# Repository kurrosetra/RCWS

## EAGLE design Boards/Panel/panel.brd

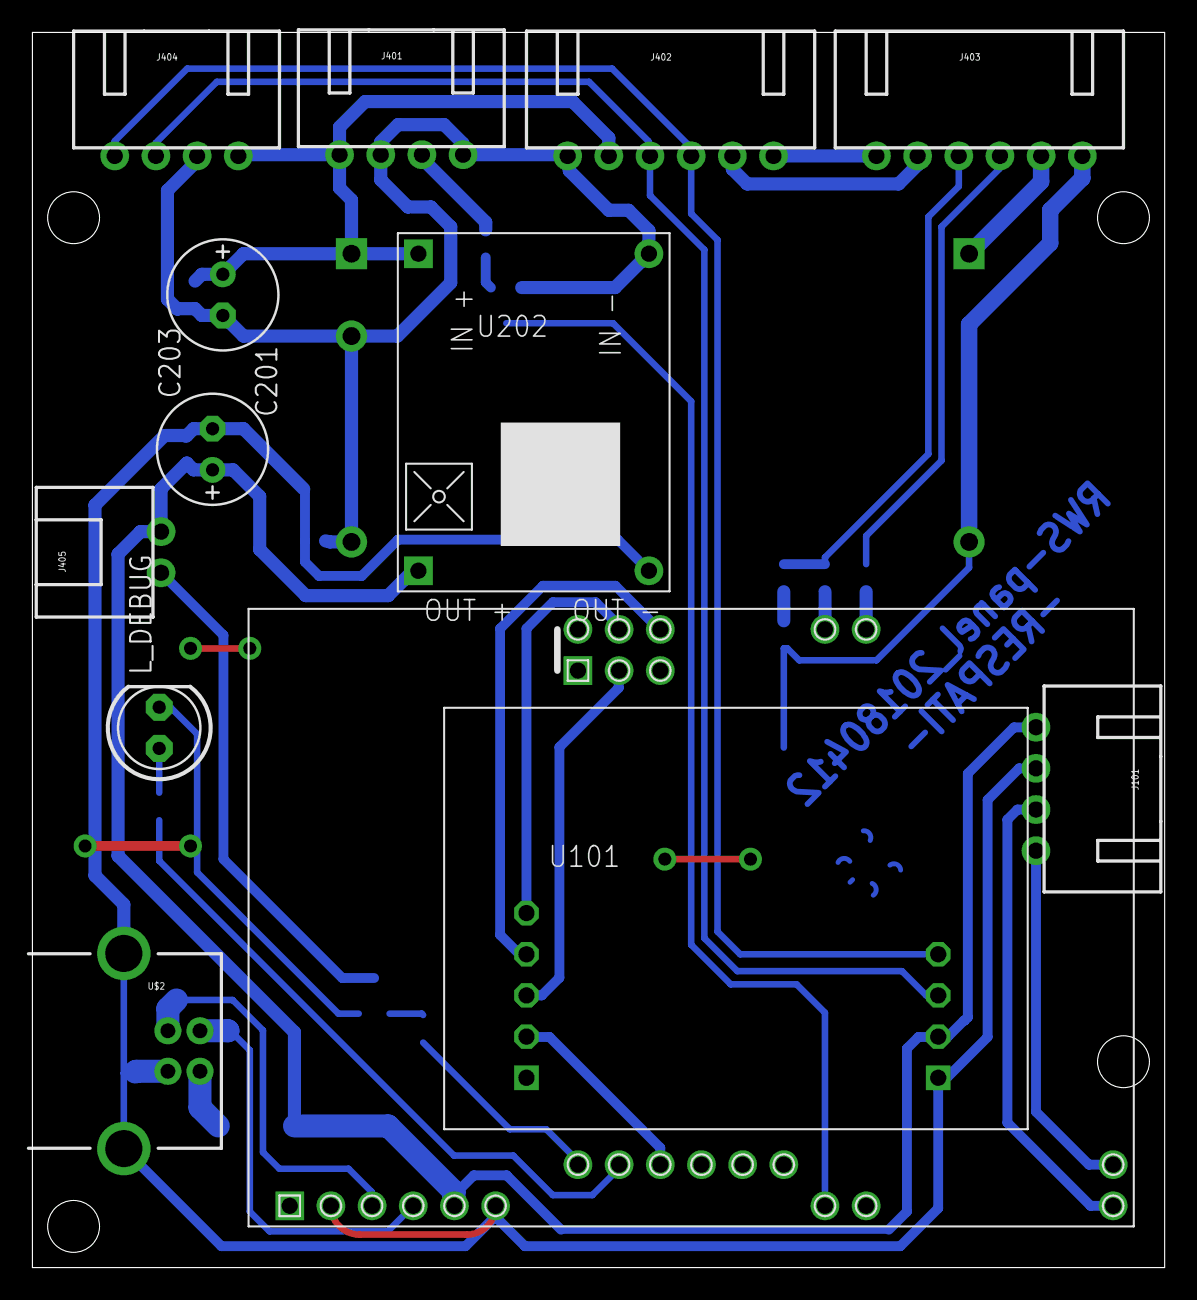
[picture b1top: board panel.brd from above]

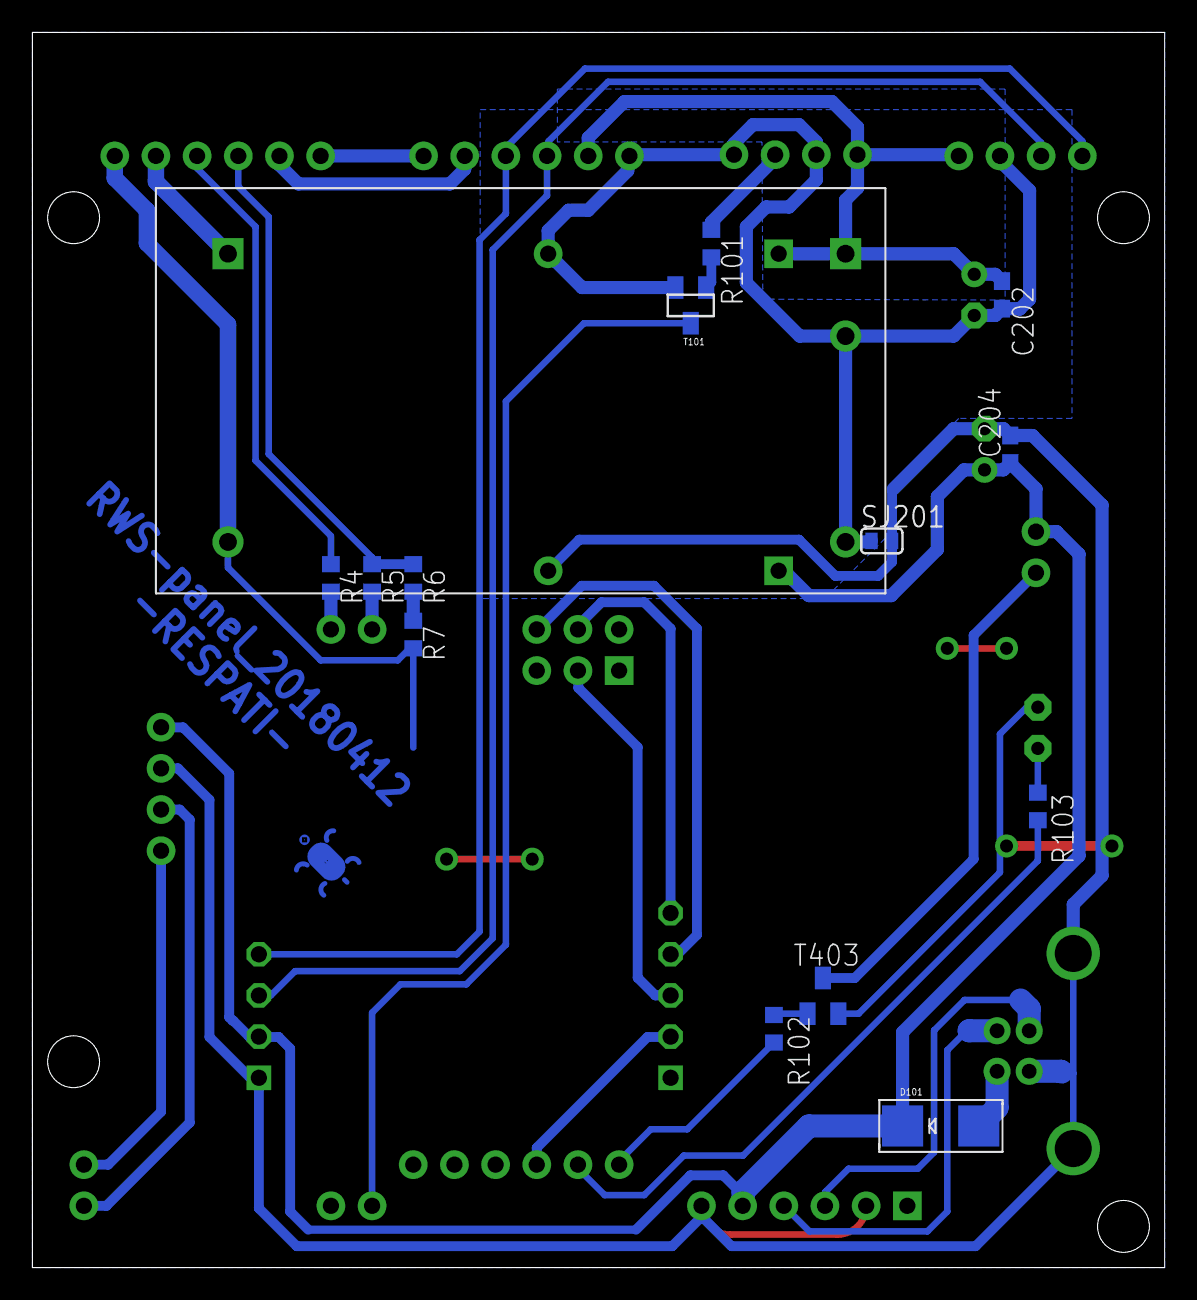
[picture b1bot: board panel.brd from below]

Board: 2 copper layers, 69.8 x 76.2 mm, 33 parts (13 on the bottom side), 31 nets.

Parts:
C201: 47uF/50V; E2,5-7
C202, C204: 100n; C0603
C203: 100uF/25V; E2,5-7
D101: 1N5822; SMADIODE
J101: RESV; XH-4-RA
J401: POWER_IN; XH-4-RA
J402: OPTRONIK; XH-6-RA
J403: JETSON; XH-6-RA
J404: JOYSTICK+MONITOR; XH-4-RA
J405: INDICATOR; XH-2-RA
L_DEBUG: LED5MM
R4, R101: 100; R0603
R5, R6, R7, R102, R103: 1k; R0603
SJ201: SJS
T101: MMBT2222A; SOT23
T403: SOT23-BEC
U1: MCP2515_CAN2
U101: MODULE_MEGA2560; MOD_MEGA_LAYOUT
U201: PSU_5V; MP1584_MIN
U202: PSU_12V; MOD_LM2596
U$1: KURRO_FOOTPRINT; KURRO-LOGO
U$2: USB+SHIELD; USB-B-PTH
U$3: MOD_MEGA_LAYOUT_SERIAL1
U$4: MOD_MEGA_LAYOUT_SERIAL2
U$5: MOD_MEGA_LAYOUT_SERIAL3
U$6: MOD_MEGA_LAYOUT_ICSP
U$7: MOD_MEGA_LAYOUT_Y_EVEN

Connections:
+15V: J403.5, U202.2
+24V: C201.+, C202.1, J401.1, J402.2, J404.4, U201.1, U202.1
BUS_CANH: J402.3, J404.2, U1.3
BUS_CANL: J402.4, J404.1, U1.4
BUS_CS: U1.6, U$7.Y6
BUTTON_TX: J401.3, R101.1
BUTTON_TXD: T101.3, U$3.Y16
GND: C203.-, C204.2, J101.2, J403.6, L_DEBUG.K, R7.2, SJ201.2, T403.E, U1.1, U101.P2, U101.P6, U201.4, U202.4, U$2.GND, U$2.S1, U$2.S2
INDICATOR_RTN: J405.1, T403.C
JETSON_RX: J403.3, R5.1, R6.1
JETSON_RXD: R5.2, U$4.X5
JETSON_TX: J403.4, R4.1
JETSON_TXD: R4.2, U$4.X8
MISO: U1.8, U$6.S6
MOSI: U1.7, U$6.S3
unnamed: R102.1, T403.B
unnamed: U101.P3, U$2.D+
unnamed: U101.P4, U$2.D-
unnamed: D101.A, U$2.VBUS
unnamed: R102.2, U$7.Y2
unnamed: R101.2, T101.1
unnamed: L_DEBUG.A, R103.1
unnamed: R103.2, U$7.Y4
unnamed: R6.2, R7.1
RESV_RXD: J101.4, U$5.Z10
RESV_TXD: J101.3, U$5.Z9
SCK: U1.9, U$6.S4
V-: C201.-, C202.2, J401.2, J401.4, J402.1, J404.3, SJ201.1, T101.2, U201.2, U202.3, U202.5
VCC: C203.+, C204.1, D101.C, J101.1, J405.2, U1.2, U101.P5, U201.3
VIDEO+: J402.5, J403.2
VIDEO-: J402.6, J403.1

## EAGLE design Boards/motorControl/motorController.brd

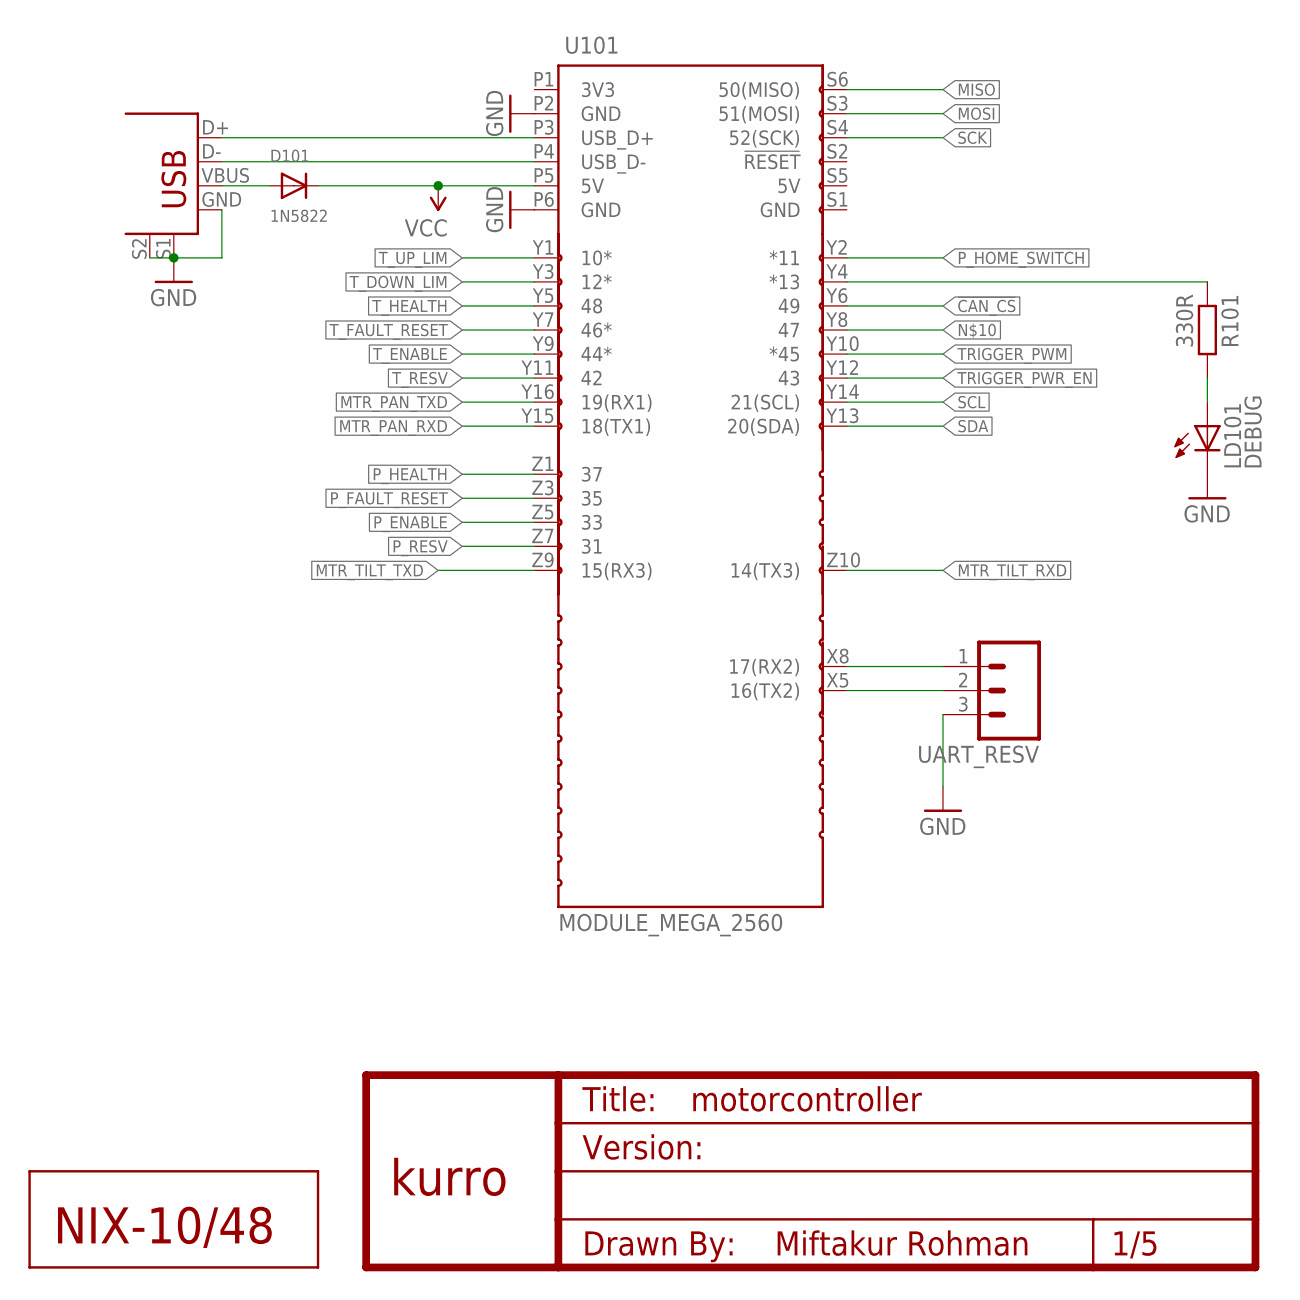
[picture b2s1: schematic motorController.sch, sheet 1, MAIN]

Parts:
D101: 1N5822; SMADIODE
J101: USB+SHIELD; USB-B-PTH
LD101: DEBUG; LED5MM
R101: 330R; R0603
U101: MODULE_MEGA_2560; MOD_MEGA_LAYOUT
U$1: KURRO_FOOTPRINT; KURRO-LOGO
U$2: NIX; NIX-XX/XXX
U$3: MOD_MEGA_LAYOUT_ICSP
U$4: MOD_MEGA_LAYOUT_SERIAL1
U$5: MOD_MEGA_LAYOUT_SERIAL2
U$6: MOD_MEGA_LAYOUT_SERIAL3
U$7: MOD_MEGA_LAYOUT_Y_EVEN
U$8: MOD_MEGA_LAYOUT_Y_ODD
U$9: MOD_MEGA_LAYOUT_Z_ODD
U$10: MOD_MEGA_LAYOUT_I2C
UART_RESV: M03LOCK; 1X03_LOCK

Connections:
!CAN_CS: U$7.Y6 (49); also elsewhere on the board
GND: J101.GND, J101.S1, J101.S2, LD101.K (C), U101.P2 (GND), U101.P6 (GND), UART_RESV.3; also elsewhere on the board
MISO: U$3.S6 (50(MISO)); also elsewhere on the board
MOSI: U$3.S3 (51(MOSI)); also elsewhere on the board
MTR_PAN_RXD: U$4.Y15 (18(TX1)); also elsewhere on the board
MTR_PAN_TXD: U$4.Y16 (19(RX1)); also elsewhere on the board
MTR_TILT_RXD: U$6.Z10 (14(TX3)); also elsewhere on the board
MTR_TILT_TXD: U$6.Z9 (15(RX3)); also elsewhere on the board
unnamed: LD101.A, R101.2
unnamed: J101.D+, U101.P3 (USB_D+)
unnamed: R101.1, U$7.Y4 (*13)
unnamed: J101.D-, U101.P4 (USB_D-)
unnamed: D101.A, J101.VBUS
P_ENABLE: U$9.Z5 (33); also elsewhere on the board
P_FAULT_RESET: U$9.Z3 (35); also elsewhere on the board
P_HEALTH: U$9.Z1 (37); also elsewhere on the board
P_HOME_SWITCH: U$7.Y2 (*11); also elsewhere on the board
P_RESV: U$9.Z7 (31); also elsewhere on the board
RXD2: U$5.X8 (17(RX2)), UART_RESV.1
SCK: U$3.S4 (52(SCK)); also elsewhere on the board
SCL: U$10.Y14 (21(SCL))
SDA: U$10.Y13 (20(SDA))
TRIGGER_PWM: U$7.Y10 (*45); also elsewhere on the board
TRIGGER_PWR_EN: U$7.Y12 (43); also elsewhere on the board
TXD2: U$5.X5 (16(TX2)), UART_RESV.2
T_DOWN_LIM: U$8.Y3 (12*); also elsewhere on the board
T_ENABLE: U$8.Y9 (44*); also elsewhere on the board
T_FAULT_RESET: U$8.Y7 (46*); also elsewhere on the board
T_HEALTH: U$8.Y5 (48); also elsewhere on the board
T_RESV: U$8.Y11 (42); also elsewhere on the board
T_UP_LIM: U$8.Y1 (10*); also elsewhere on the board
VCC: D101.C, U101.P5 (5V); also elsewhere on the board

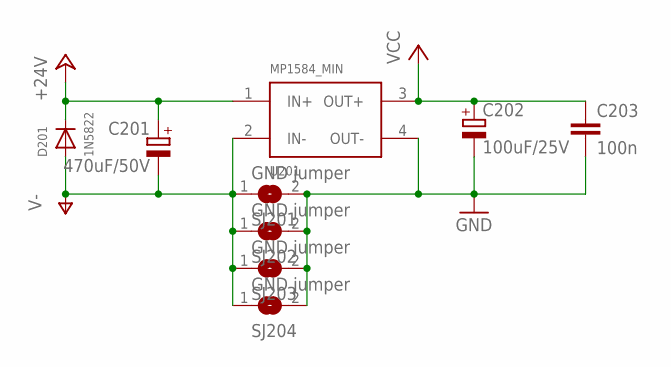
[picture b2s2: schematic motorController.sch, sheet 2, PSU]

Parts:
C201: 470uF/50V; E5-10,5
C202: 100uF/25V; E5-10,5
C203: 100n; C0603
D201: 1N5822; SMADIODE
SJ201, SJ202, SJ203, SJ204: GND jumper; SJS
U201: MP1584_MIN

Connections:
+24V: C201.+, D201.C, U201.1 (IN+); also elsewhere on the board
GND: C202.-, C203.2, SJ201.2, SJ202.2, SJ203.2, SJ204.2, U201.4 (OUT-); also elsewhere on the board
V-: C201.-, D201.A, SJ201.1, SJ202.1, SJ203.1, SJ204.1, U201.2 (IN-); also elsewhere on the board
VCC: C202.+, C203.1, U201.3 (OUT+); also elsewhere on the board

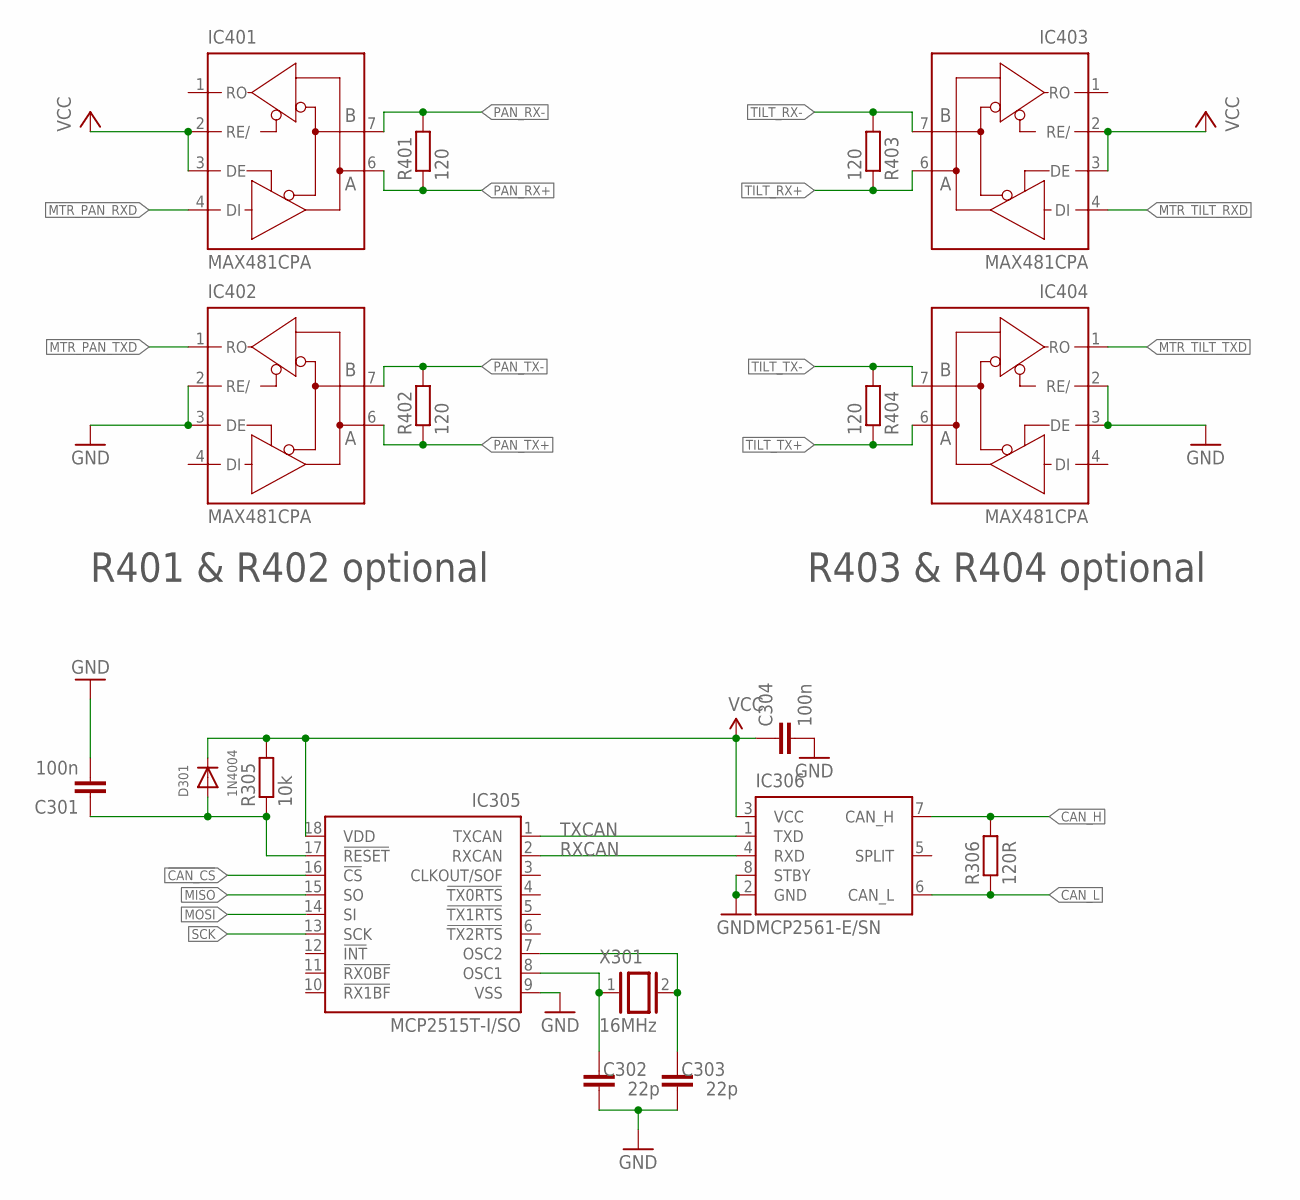
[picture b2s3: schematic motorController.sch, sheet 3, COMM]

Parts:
C301, C304: 100n; C0603
C302, C303: 22p; C0603
D301: 1N4004; SOD-323F
IC305: MCP2515T-I/SO; SO-18
IC306: MCP2561-E/SN; SOIC-8
IC401, IC402, IC403, IC404: MAX481CPA; DIL08
R305: 10k; R0603
R306: 120R; R0603
R401, R402, R403, R404: 120; R0603
X301: 16MHz; QS

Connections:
!CAN_CS: IC305.16 (!CS); also elsewhere on the board
CAN_H: IC306.7 (CAN_H), R306.2; also elsewhere on the board
CAN_L: IC306.6 (CAN_L), R306.1; also elsewhere on the board
GND: C301.2, C302.1, C303.1, C304.2, IC305.9 (VSS), IC306.2 (GND), IC306.8 (STBY), IC401.5 (GND), IC402.2 (RE/), IC402.3 (DE), IC402.5 (GND), IC403.5 (GND), IC404.2 (RE/), IC404.3 (DE), IC404.5 (GND); also elsewhere on the board
MISO: IC305.15 (SO); also elsewhere on the board
MOSI: IC305.14 (SI); also elsewhere on the board
MTR_PAN_RXD: IC401.4 (DI); also elsewhere on the board
MTR_PAN_TXD: IC402.1 (RO); also elsewhere on the board
MTR_TILT_RXD: IC403.4 (DI); also elsewhere on the board
MTR_TILT_TXD: IC404.1 (RO); also elsewhere on the board
unnamed: C301.1, D301.A, IC305.17 (!RESET), R305.1
unnamed: C302.2, IC305.8 (OSC1), X301.1
unnamed: C303.2, IC305.7 (OSC2), X301.2
PAN_RX+: IC401.6 (A), R401.1; also elsewhere on the board
PAN_RX-: IC401.7 (B), R401.2; also elsewhere on the board
PAN_TX+: IC402.6 (A), R402.1; also elsewhere on the board
PAN_TX-: IC402.7 (B), R402.2; also elsewhere on the board
RXCAN: IC305.2 (RXCAN), IC306.4 (RXD)
SCK: IC305.13 (SCK); also elsewhere on the board
TILT_RX+: IC403.6 (A), R403.1; also elsewhere on the board
TILT_RX-: IC403.7 (B), R403.2; also elsewhere on the board
TILT_TX+: IC404.6 (A), R404.1; also elsewhere on the board
TILT_TX-: IC404.7 (B), R404.2; also elsewhere on the board
TXCAN: IC305.1 (TXCAN), IC306.1 (TXD)
VCC: C304.1, D301.C, IC305.18 (VDD), IC306.3 (VCC), IC401.2 (RE/), IC401.3 (DE), IC401.8 (VCC), IC402.8 (VCC), IC403.2 (RE/), IC403.3 (DE), IC403.8 (VCC), IC404.8 (VCC), R305.2; also elsewhere on the board

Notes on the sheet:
R401 & R402 optional
R403 & R404 optional

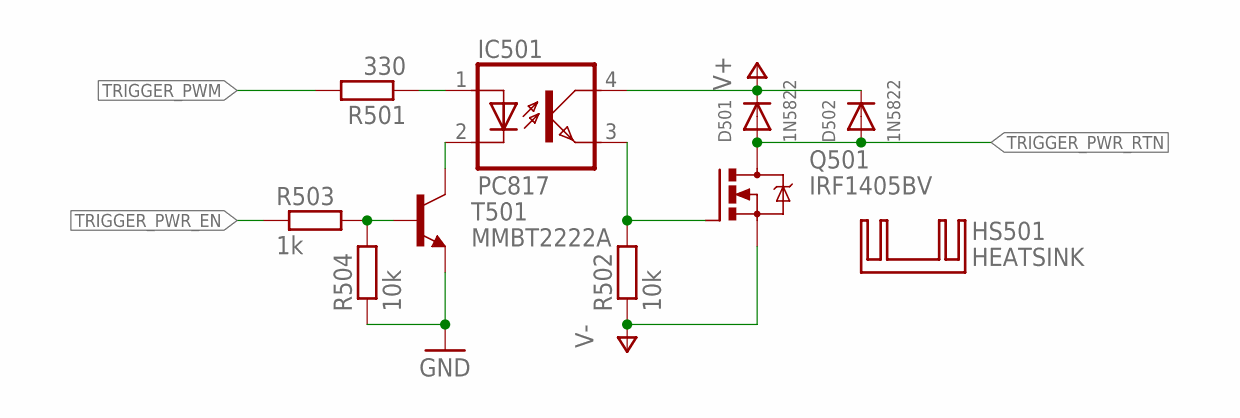
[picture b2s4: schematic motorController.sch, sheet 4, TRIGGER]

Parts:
D501, D502: 1N5822; SMADIODE
HS501: HEATSINK; BV_150X105
IC501: PC817; DIL04
Q501: IRF1405BV; TO220BV
R501: 330; R0603
R502, R504: 10k; R0603
R503: 1k; R0603
T501: MMBT2222A; SOT23

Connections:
GND: R504.1, T501.2 (E); also elsewhere on the board
unnamed: IC501.2 (C), T501.3 (C)
unnamed: R503.2, R504.2, T501.1 (B)
unnamed: IC501.1 (A), R501.1
unnamed: IC501.3 (EMIT), Q501.G, R502.2
TRIGGER_PWM: R501.2; also elsewhere on the board
TRIGGER_PWR_EN: R503.1; also elsewhere on the board
TRIGGER_PWR_RTN: D501.A, D502.A, Q501.D; also elsewhere on the board
V+: D501.C, D502.C, IC501.4 (COL); also elsewhere on the board
V-: Q501.S, R502.1; also elsewhere on the board

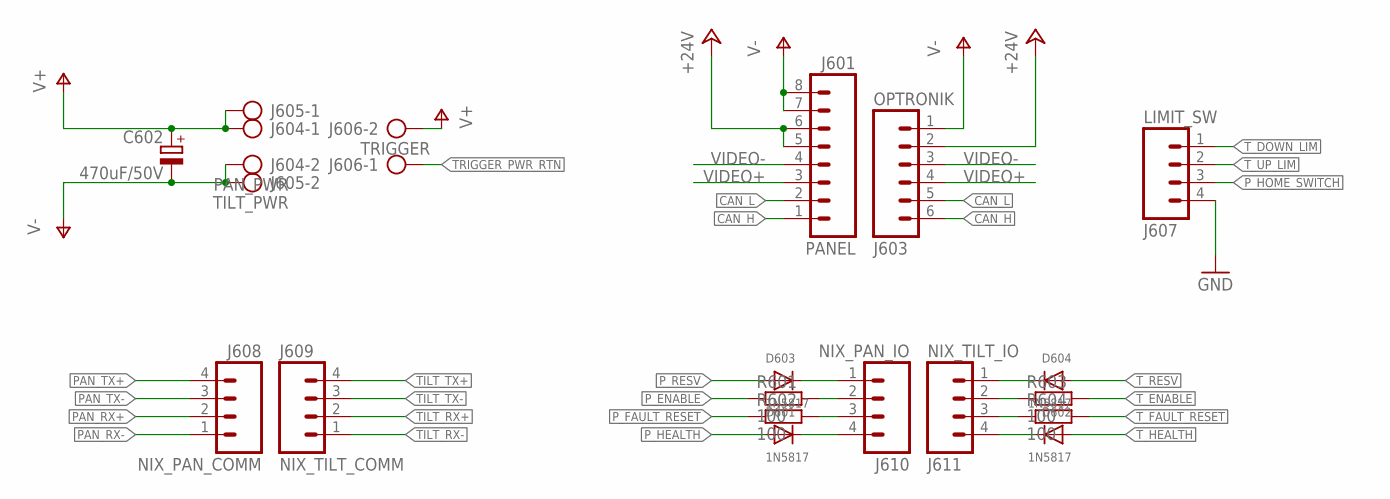
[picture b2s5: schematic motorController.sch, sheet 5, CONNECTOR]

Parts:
C602: 470uF/50V; E5-10,5
D601, D602, D603, D604: 1N5817; SOD-323F
J601: PANEL; XH-8-RA
J603: OPTRONIK; XH-6-RA
J604: PAN_PWR; AK200/2
J605: TILT_PWR; AK200/2
J606: TRIGGER; AK200/2
J607: LIMIT_SW; XH-4-RA
J608: NIX_PAN_COMM; XH-4-RA
J609: NIX_TILT_COMM; XH-4-RA
J610: NIX_PAN_IO; XH-4-RA
J611: NIX_TILT_IO; XH-4-RA
R601, R602, R603, R604: 100; R0603

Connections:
+24V: J601.5, J601.6, J603.2; also elsewhere on the board
CAN_H: J601.1, J603.6; also elsewhere on the board
CAN_L: J601.2, J603.5; also elsewhere on the board
GND: J607.4; also elsewhere on the board
unnamed: D603.C, J610.1
unnamed: D604.C, J611.1
unnamed: J611.2, R603.1
unnamed: J611.3, R604.1
unnamed: D602.C, J611.4
unnamed: D601.C, J610.4
unnamed: J610.2, R601.2
unnamed: J610.3, R602.2
PAN_RX+: J608.2; also elsewhere on the board
PAN_RX-: J608.1; also elsewhere on the board
PAN_TX+: J608.4; also elsewhere on the board
PAN_TX-: J608.3; also elsewhere on the board
P_ENABLE: R601.1; also elsewhere on the board
P_FAULT_RESET: R602.1; also elsewhere on the board
P_HEALTH: D601.A; also elsewhere on the board
P_HOME_SWITCH: J607.3; also elsewhere on the board
P_RESV: D603.A; also elsewhere on the board
TILT_RX+: J609.2; also elsewhere on the board
TILT_RX-: J609.1; also elsewhere on the board
TILT_TX+: J609.4; also elsewhere on the board
TILT_TX-: J609.3; also elsewhere on the board
TRIGGER_PWR_RTN: J606.1; also elsewhere on the board
T_DOWN_LIM: J607.1; also elsewhere on the board
T_ENABLE: R603.2; also elsewhere on the board
T_FAULT_RESET: R604.2; also elsewhere on the board
T_HEALTH: D602.A; also elsewhere on the board
T_RESV: D604.A; also elsewhere on the board
T_UP_LIM: J607.2; also elsewhere on the board
V+: C602.+, J604.1, J605.1, J606.2; also elsewhere on the board
V-: C602.-, J601.7, J601.8, J603.1, J604.2, J605.2; also elsewhere on the board
VIDEO+: J601.3, J603.4
VIDEO-: J601.4, J603.3

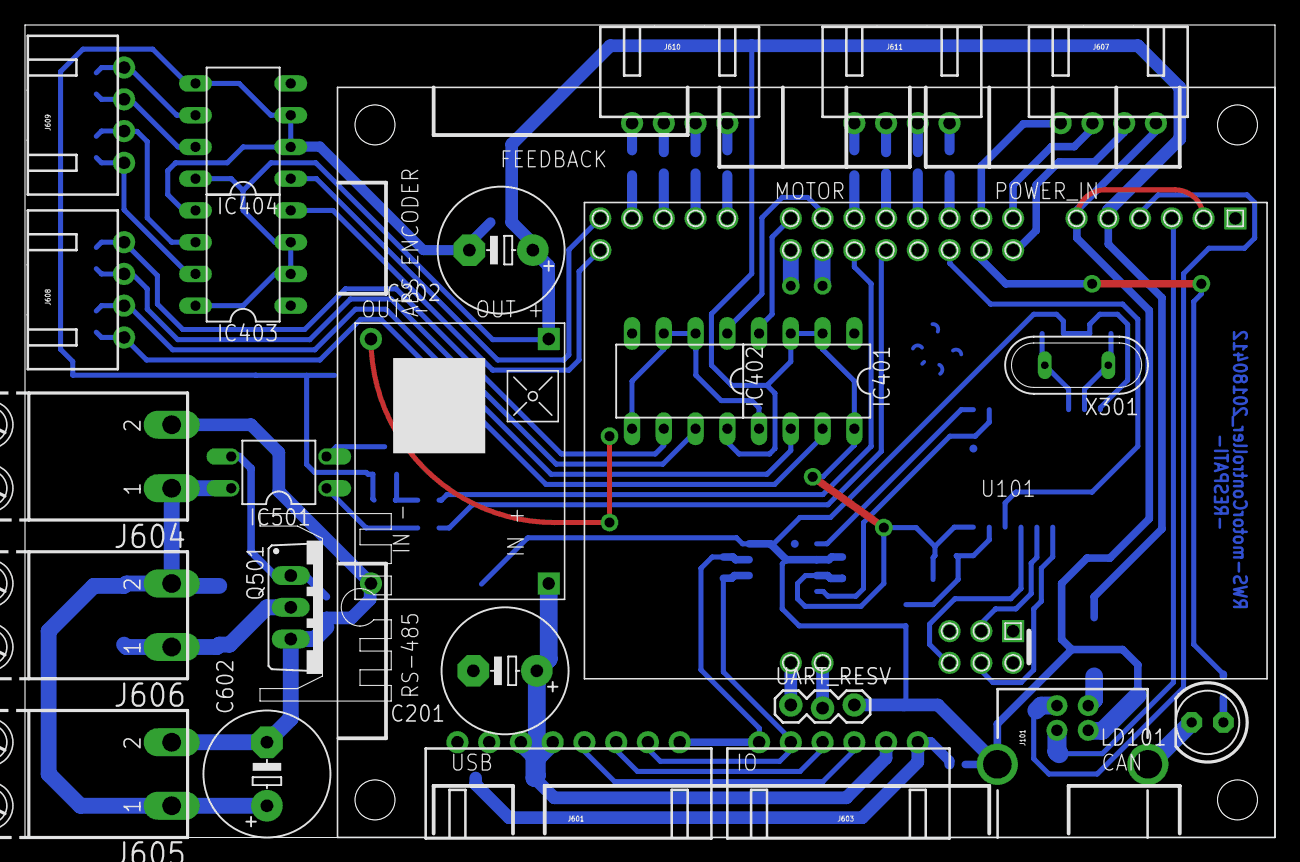
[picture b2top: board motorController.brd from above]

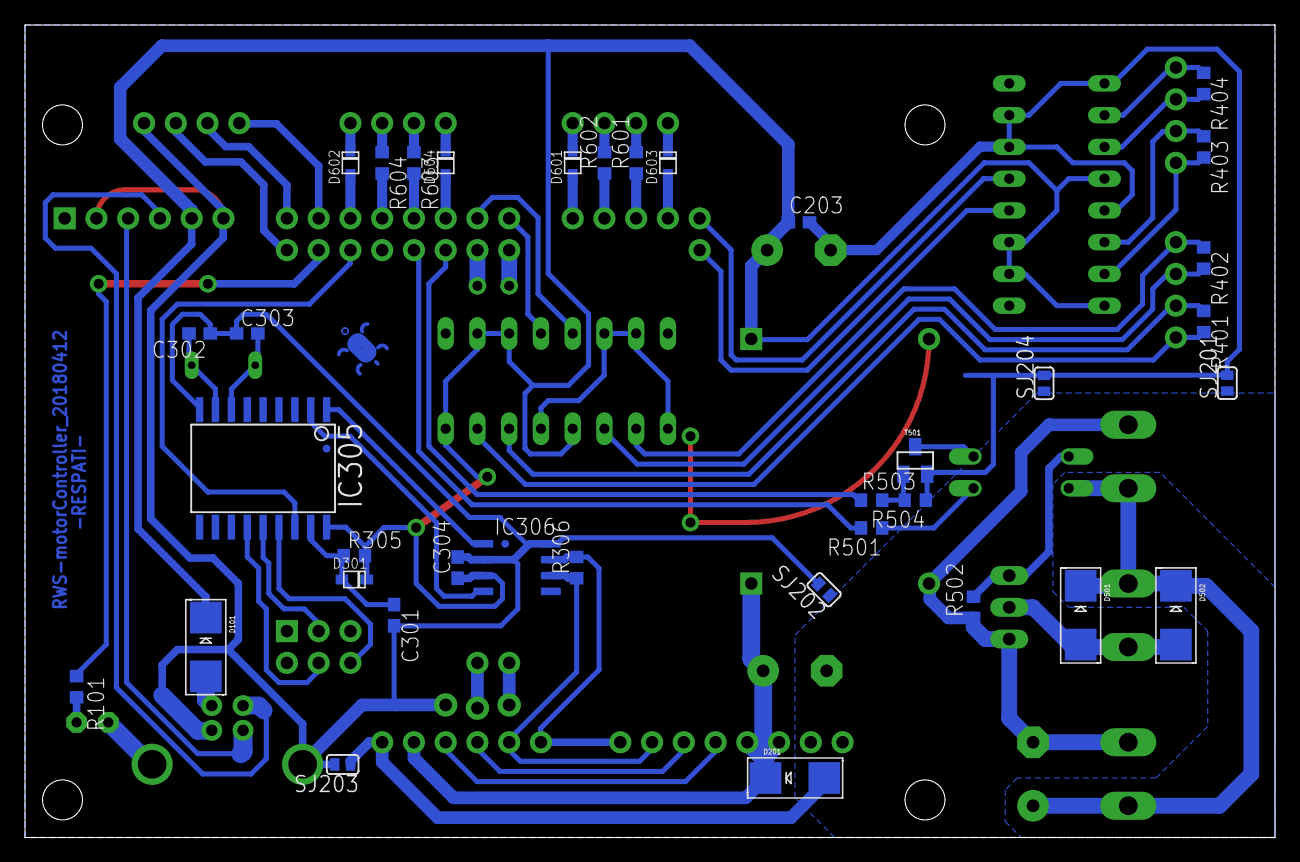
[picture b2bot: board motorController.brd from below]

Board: 2 copper layers, 100.0 x 65.0 mm, 72 parts (36 on the bottom side), 63 nets.

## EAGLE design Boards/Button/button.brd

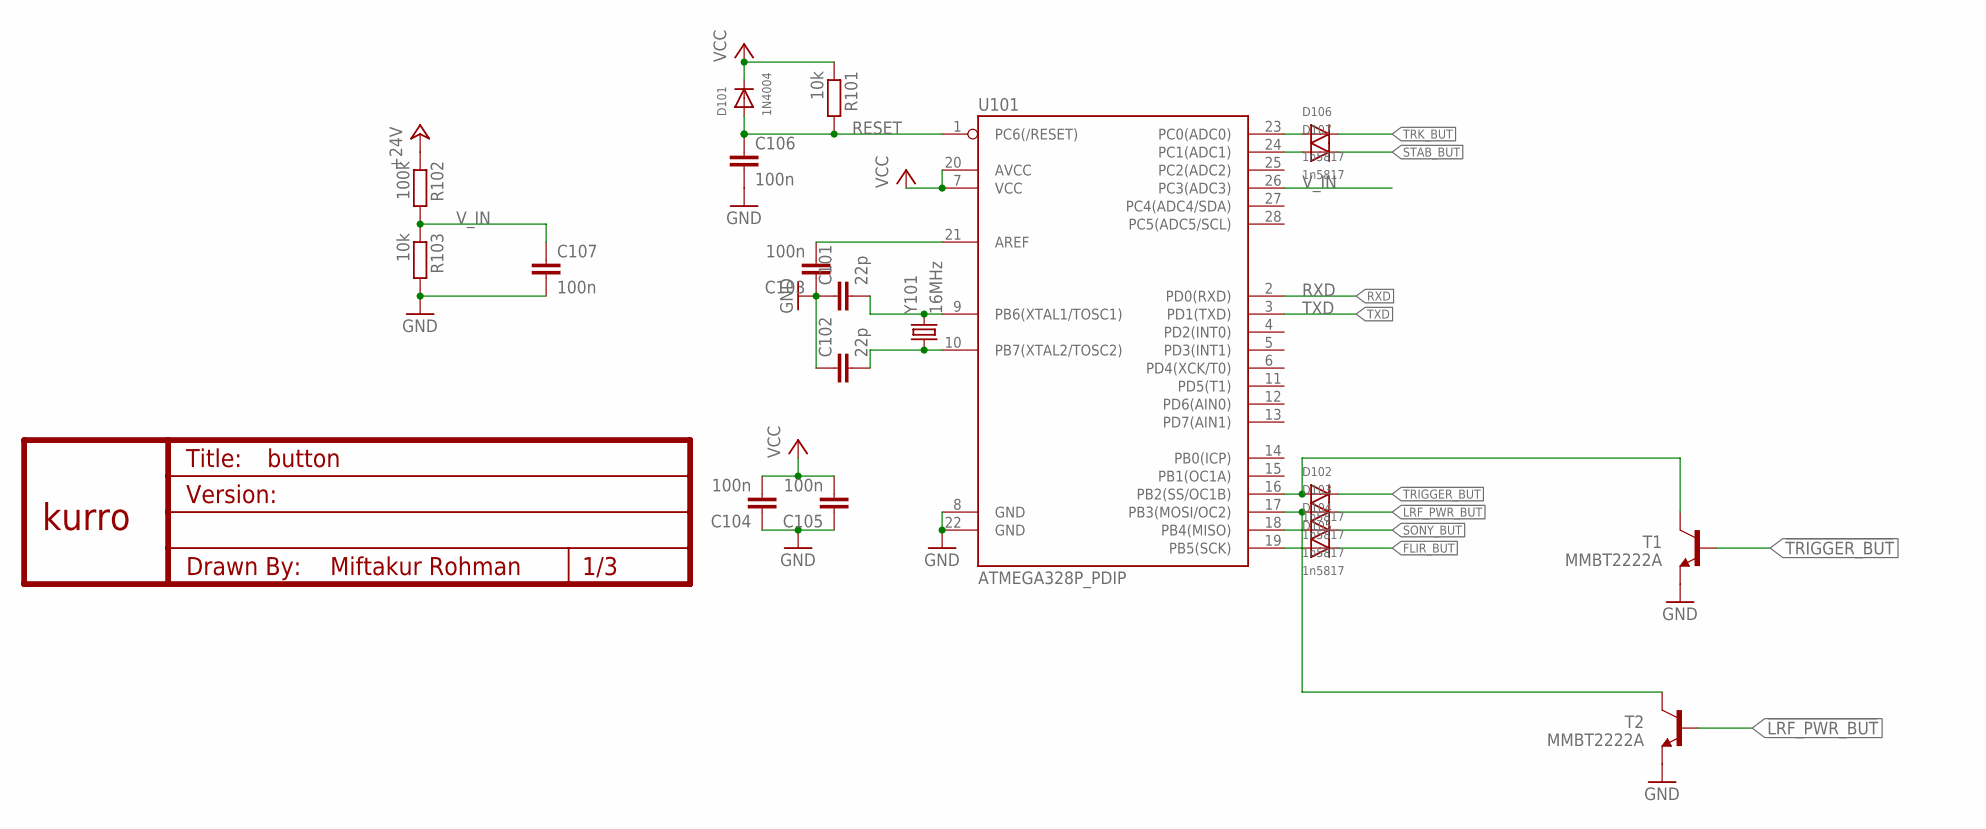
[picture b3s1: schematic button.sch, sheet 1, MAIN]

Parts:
C101, C102: 22p; C0603
C103, C104, C105, C106, C107: 100n; C0603
D101: 1N4004; SOD-323F
D102, D103, D104, D105, D106, D107: 1n5817; SOD-323F
R101, R103: 10k; R0603
R102: 100k; R0603
T1, T2: MMBT2222A; SOT23
U101: ATMEGA328P_PDIP; DIL28-3
U$1: KURRO_FOOTPRINT; KURRO-LOGO
Y101: 16MHz; CRYSTAL-TXC-7A2

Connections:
!LRF_PWR_BUT: D103.C, T2.1 (B); also elsewhere on the board
!TRIGGER_BUT: D102.C, T1.1 (B); also elsewhere on the board
+24V: R102.1; also elsewhere on the board
FLIR_BUT: D105.C; also elsewhere on the board
GND: C101.1, C102.1, C103.1, C104.1, C105.1, C106.2, C107.2, R103.2, T1.2 (E), T2.2 (E), U101.8 (GND), U101.22 (GND); also elsewhere on the board
unnamed: D104.A, U101.18 (PB4(MISO))
unnamed: D105.A, U101.19 (PB5(SCK))
unnamed: D103.A, T2.3 (C), U101.17 (PB3(MOSI/OC2))
unnamed: D106.A, U101.23 (PC0(ADC0))
unnamed: D107.A, U101.24 (PC1(ADC1))
unnamed: D102.A, T1.3 (C), U101.16 (PB2(SS/OC1B))
unnamed: C101.2, U101.9 (PB6(XTAL1/TOSC1)), Y101.P$2 (2)
unnamed: C102.2, U101.10 (PB7(XTAL2/TOSC2)), Y101.P$1 (1)
unnamed: C103.2, U101.21 (AREF)
RESET: C106.1, D101.A, R101.2, U101.1 (PC6(/RESET))
RXD: U101.2 (PD0(RXD))
SONY_BUT: D104.C; also elsewhere on the board
STAB_BUT: D107.C; also elsewhere on the board
TRK_BUT: D106.C; also elsewhere on the board
TXD: U101.3 (PD1(TXD)); also elsewhere on the board
VCC: C104.2, C105.2, D101.C, R101.1, U101.7 (VCC), U101.20 (AVCC); also elsewhere on the board
V_IN: C107.1, R102.2, R103.1, U101.26 (PC3(ADC3))

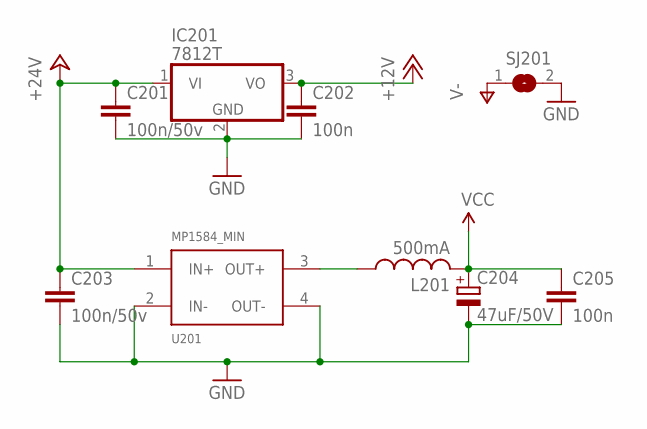
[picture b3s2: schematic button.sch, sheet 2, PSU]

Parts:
C201, C203: 100n/50v; C0603
C202, C205: 100n; C0603
C204: 47uF/50V; E2,5-7
IC201: 7812T; TO220H
L201: 500mA; L1812
SJ201: SJ
U201: MP1584_MIN

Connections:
+12V: C202.1, IC201.3 (VO); also elsewhere on the board
+24V: C201.1, C203.1, IC201.1 (VI), U201.1 (IN+); also elsewhere on the board
GND: C201.2, C202.2, C203.2, C204.-, C205.2, IC201.2 (GND), SJ201.2, U201.2 (IN-), U201.4 (OUT-); also elsewhere on the board
unnamed: L201.1, U201.3 (OUT+)
V-: SJ201.1; also elsewhere on the board
VCC: C204.+, C205.1, L201.2; also elsewhere on the board

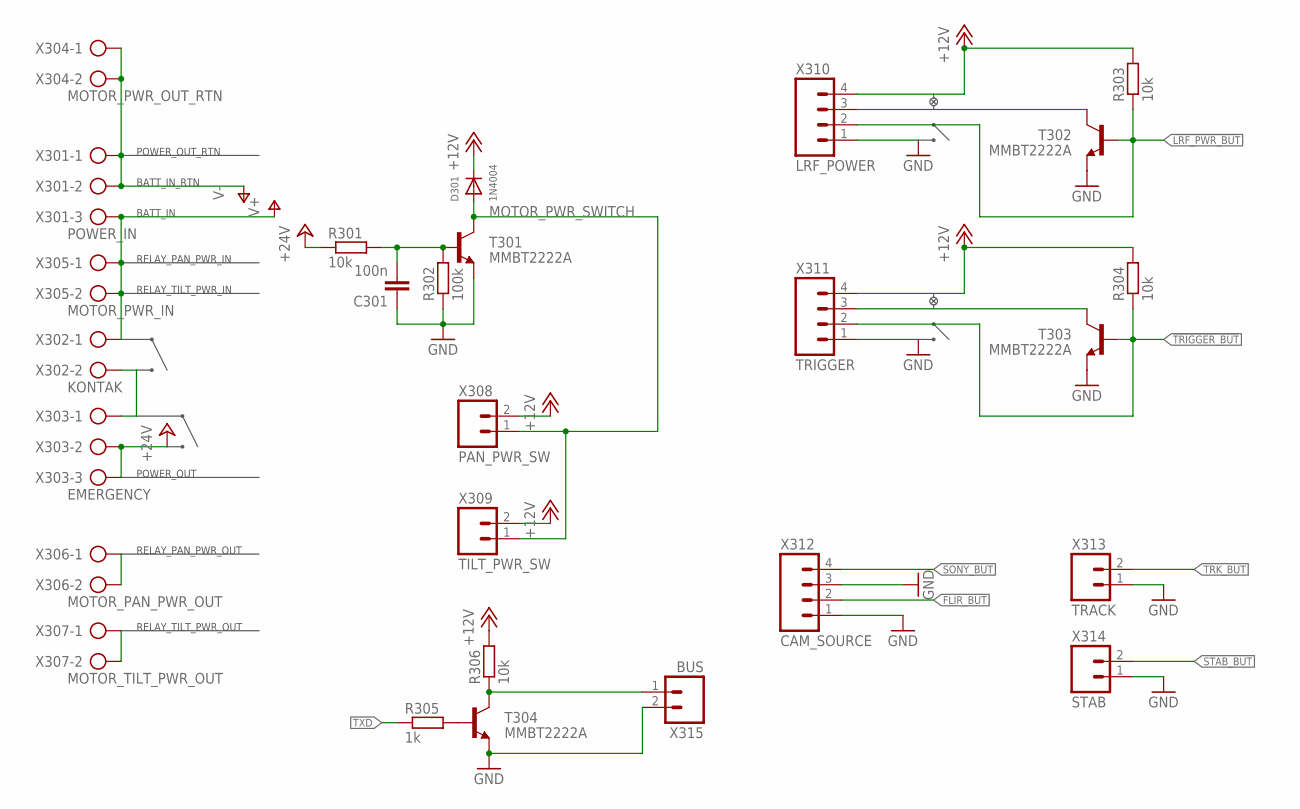
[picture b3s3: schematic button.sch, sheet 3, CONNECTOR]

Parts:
C301: 100n; C0603
D301: 1N4004; SOD-323F
R301, R303, R304, R306: 10k; R0603
R302: 100k; R0603
R305: 1k; R0603
T301, T302, T303, T304: MMBT2222A; SOT23
X301: POWER_IN; AK300/3
X302: KONTAK; AK300/2
X303: EMERGENCY; AK300/3
X304: MOTOR_PWR_OUT_RTN; AK300/2
X305: MOTOR_PWR_IN; AK300/2
X306: MOTOR_PAN_PWR_OUT; AK300/2
X307: MOTOR_TILT_PWR_OUT; AK300/2
X308: PAN_PWR_SW; JST-2-PTH-VERT
X309: TILT_PWR_SW; JST-2-PTH-VERT
X310: LRF_POWER; JST-4-PTH-VERT
X311: TRIGGER; JST-4-PTH-VERT
X312: CAM_SOURCE; JST-4-PTH-VERT
X313: TRACK; JST-2-PTH-VERT
X314: STAB; JST-2-PTH-VERT
X315: BUS; JST-2-PTH-VERT

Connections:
!LRF_PWR_BUT: R303.1, T302.1 (B), X310.2; also elsewhere on the board
!TRIGGER_BUT: R304.1, T303.1 (B), X311.2; also elsewhere on the board
+12V: D301.C, R303.2, R304.2, R306.2, X308.2, X309.2, X310.4, X311.4; also elsewhere on the board
+24V: R301.1, X303.2, X303.3; also elsewhere on the board
BUS1: R306.1, T304.3 (C), X315.1
FLIR_BUT: X312.2; also elsewhere on the board
GND: C301.1, R302.1, T301.2 (E), T302.2 (E), T303.2 (E), T304.2 (E), X310.1, X311.1, X312.1, X312.3, X313.1, X314.1, X315.2; also elsewhere on the board
KONTAK_EMER_JUNCTION: X302.2, X303.1
MOTOR_PWR_SWITCH: D301.A, T301.3 (C), X308.1, X309.1
unnamed: C301.2, R301.2, R302.2, T301.1 (B)
unnamed: X306.1, X306.2
unnamed: X307.1, X307.2
unnamed: T303.3 (C), X311.3
unnamed: T302.3 (C), X310.3
unnamed: R305.2, T304.1 (B)
SONY_BUT: X312.4; also elsewhere on the board
STAB_BUT: X314.2; also elsewhere on the board
TRK_BUT: X313.2; also elsewhere on the board
TXD: R305.1; also elsewhere on the board
V+: X301.3, X302.1, X305.1, X305.2
V-: X301.1, X301.2, X304.1, X304.2; also elsewhere on the board

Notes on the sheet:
RELAY_PAN_PWR_IN
RELAY_TILT_PWR_IN
RELAY_PAN_PWR_OUT
RELAY_TILT_PWR_OUT
POWER_OUT_RTN
POWER_OUT
BATT_IN
BATT_IN_RTN

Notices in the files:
parts and their libraries:
SparkFun-DigitalIC: Licensing: CC v3.0 Share-Alike You are welcome to use this library for commercial purposes.
SparkFun-FreqCtrl: Licensing: Creative Commons ShareAlike 4.0 International - https://creativecommons.org/licenses/by-sa/4.0
